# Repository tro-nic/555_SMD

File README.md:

# 555_SMD
Small board to use in breadboads projects.  #LM555  SMD on #PCB 4 layers,  One inch module.

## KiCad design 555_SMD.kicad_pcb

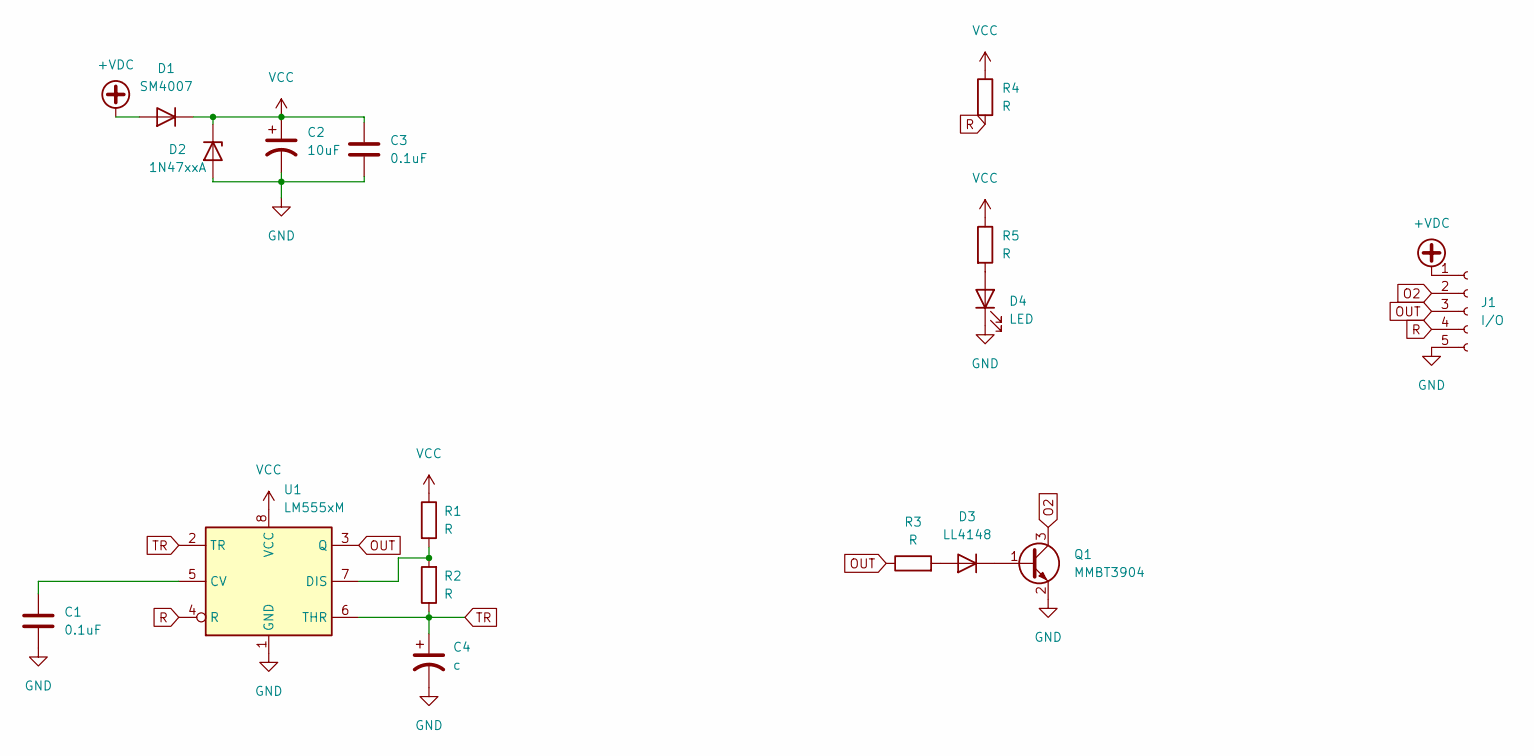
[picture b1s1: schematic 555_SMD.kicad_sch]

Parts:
C1, C3: 0.1uF; C_1206_3216Metric
C2: 10uF; CP_Elec_3x5.3
C4: c; CP_Elec_8x10
D1: SM4007; D_MELF
D2: 1N47xxA; D_DO-41_SOD81_P10.16mm_Horizontal
D3: LL4148; D_MiniMELF
D4: LED; LED_1206_3216Metric
J1: I/O; PinHeader_1x05_P2.54mm_Vertical
Q1: MMBT3904; SOT-23
R1, R2, R3, R4, R5: R; R_1206_3216Metric
U1: LM555xM; SOIC-8_3.9x4.9mm_P1.27mm

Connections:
+VDC: D1.2 (A), J1.1
GND: C1.2, C2.2, C3.2, C4.2, D2.2 (A), D4.1 (K), J1.5, Q1.2 (E), U1.1 (GND)
unnamed: C1.1, U1.5 (CV)
unnamed: D3.1 (K), Q1.1 (B)
unnamed: D3.2 (A), R3.2
unnamed: D4.2 (A), R5.2
unnamed: R1.2, R2.2, U1.7 (DIS)
O2: J1.2, Q1.3 (C)
OUT: J1.3, R3.1, U1.3 (Q)
R: J1.4, R4.2, U1.4 (R)
TR: C4.1, R2.1, U1.2 (TR), U1.6 (THR)
VCC: C2.1, C3.1, D1.1 (K), D2.1 (K), R1.1, R4.1, R5.1, U1.8 (VCC)

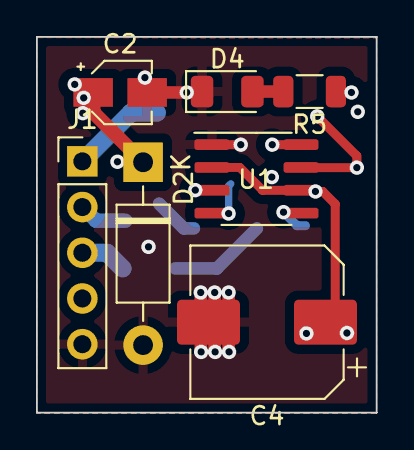
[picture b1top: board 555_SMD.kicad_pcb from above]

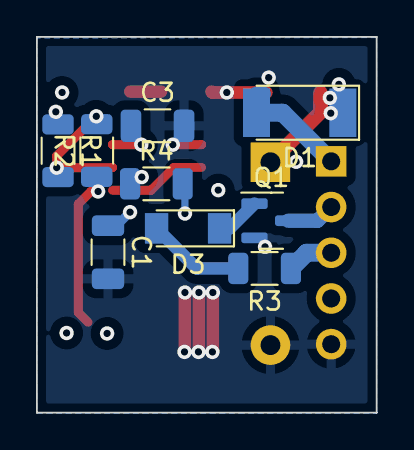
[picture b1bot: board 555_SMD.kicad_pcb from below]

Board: 4 copper layers, 18.9 x 20.9 mm, 16 parts (9 on the bottom side), 12 nets.
